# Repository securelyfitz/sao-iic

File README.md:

# sao-iic
Addon to common IIC pinouts

See the main [microbadge](https://github.com/securelyfitz/microbadge) page for more details

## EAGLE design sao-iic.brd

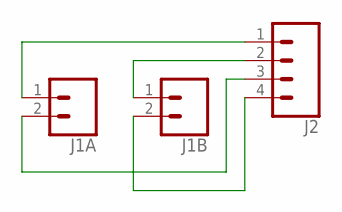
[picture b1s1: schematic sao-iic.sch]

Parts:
J1A, J1B: CONN_02LOCK; 1X02_LOCK
J2: CONN_04LOCK; 1X04_LOCK

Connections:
V1: J1A.1, J2.1
V2: J1B.1, J2.2
V3: J1A.2, J2.3
V4: J1B.2, J2.4

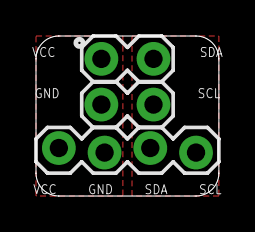
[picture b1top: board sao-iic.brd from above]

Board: 2 copper layers, 10.2 x 8.9 mm, 3 parts (0 on the bottom side), 4 nets.

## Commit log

2018-08-09 boards, schematics, gerbers, and zips...

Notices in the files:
parts and their libraries:
SparkFun-Connectors: Licensing: Creative Commons ShareAlike 4.0 International - https://creativecommons.org/licenses/by-sa/4.0
